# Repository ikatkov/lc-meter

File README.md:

# lc-meter
AADE design LC meter

arduino internal xtal is callibrated to 2ppm with Rigol DS1054Z hardware freq counter, used to be 500ppm off

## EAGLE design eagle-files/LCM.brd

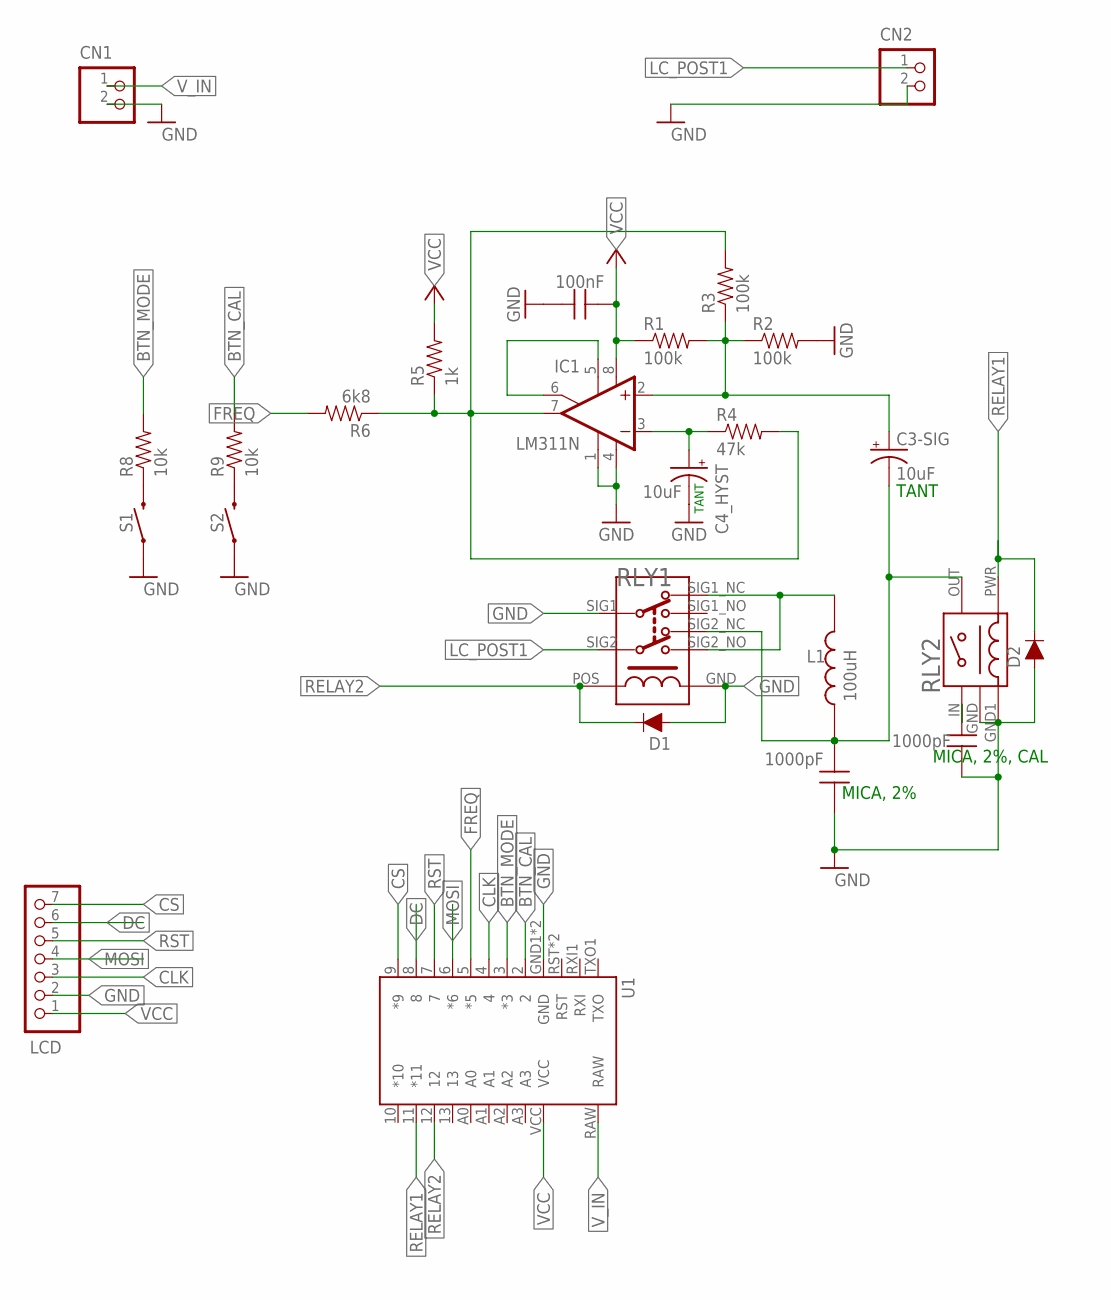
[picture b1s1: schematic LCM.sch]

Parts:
C1, C2: 1000pF; CAPACITOR_PITCH3
C3-SIG, C4_HYST: 10uF; CAPACITOR_POLAR
C5: 100nF; CAPACITOR_PITCH4
CN1, CN2: CONNECTOR-JST-2
D1, D2: DIODEPITCH_3; DIODE_PITCH3
IC1: LM311N; DIL08
L1: 100uH; INDUCTOR-12.5MM
LCD: CONNECTOR-JST-7
R1: 100k; RESISTOR_PITCH5
R2: 100k; RESISTOR_PITCH3
R3: 100k; RESISTOR_PITCH4
R4: 47k; RESISTOR_PITCH3
R5: 1k; RESISTOR_PITCH3
R6: 6k8; RESISTOR_PITCH4
R8, R9: 10k; RESISTOR_PITCH3
RLY1: RELAY_5W-KRELAY-5W-K; RELAY_5W-K
RLY2: REED_RELAY
S1, S2: MOMENTARY-SWITCH-SPST; TACTILE_SWITCH
U1: ARDUINO_PRO_MINI_NO_PRG_HEADER_NOA5NO_A5; ARDUINO_PRO_MINI_IN_HEADER_NOA5

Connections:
BTN_CAL: R9.2, U1.2
BTN_MODE: R8.2, U1.3 (*3)
CLK: LCD.3, U1.4
CS: LCD.7, U1.9 (*9)
DC: LCD.6, U1.8
FREQ: IC1.7 (OUT), R3.2, R4.2, R5.1, R6.1, R6.2, U1.5 (*5)
GND: C1.1 (+), C2.1 (+), C4_HYST.2 (-), C5.1 (+), CN1.2, CN2.2, D1.ANODE (A), D2.ANODE (A), IC1.1 (GND), IC1.4 (V-), LCD.2, R2.2, RLY1.GND (2), RLY1.SIG1, RLY2.GND, RLY2.GND1 (PWR1), S1.1, S1.2 (1), S2.1, S2.2 (1), U1.GND1 (GND), U1.GND4 (GND)
LC_POST1: CN2.1, RLY1.SIG2
MOSI: LCD.4, U1.6 (*6)
unnamed: R8.1, S1.3 (2), S1.4 (2)
unnamed: R9.1, S2.3 (2), S2.4 (2)
PIN2: C3-SIG.1 (+), IC1.2 (+IN), R1.2, R2.1, R3.1
PIN3: C4_HYST.1 (+), IC1.3 (-IN), R4.1
RELAY1: D2.CATHODE (C), RLY2.PWR (PWR2), U1.11 (*11)
RELAY2: D1.CATHODE (C), RLY1.POS (1), U1.12
RST: LCD.5, U1.7
SIG: C2.2 (-), RLY2.IN (SIG1)
SIG2_NC: C1.2 (-), C3-SIG.2 (-), L1.2, RLY1.SIG2_NC (SIG1_NC), RLY2.OUT (SIG2)
SIG2_NO: L1.1, RLY1.SIG1_NC (SIG2_NC), RLY1.SIG2_NO (SIG1_NO)
STROBE: IC1.5 (ON), IC1.6 (ON/STR)
VCC: C5.2 (-), IC1.8 (V+), LCD.1, R1.1, R5.2, U1.VCC
V_IN: CN1.1, U1.RAW

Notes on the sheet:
MICA, 2%
TANT
MICA, 2%, CAL

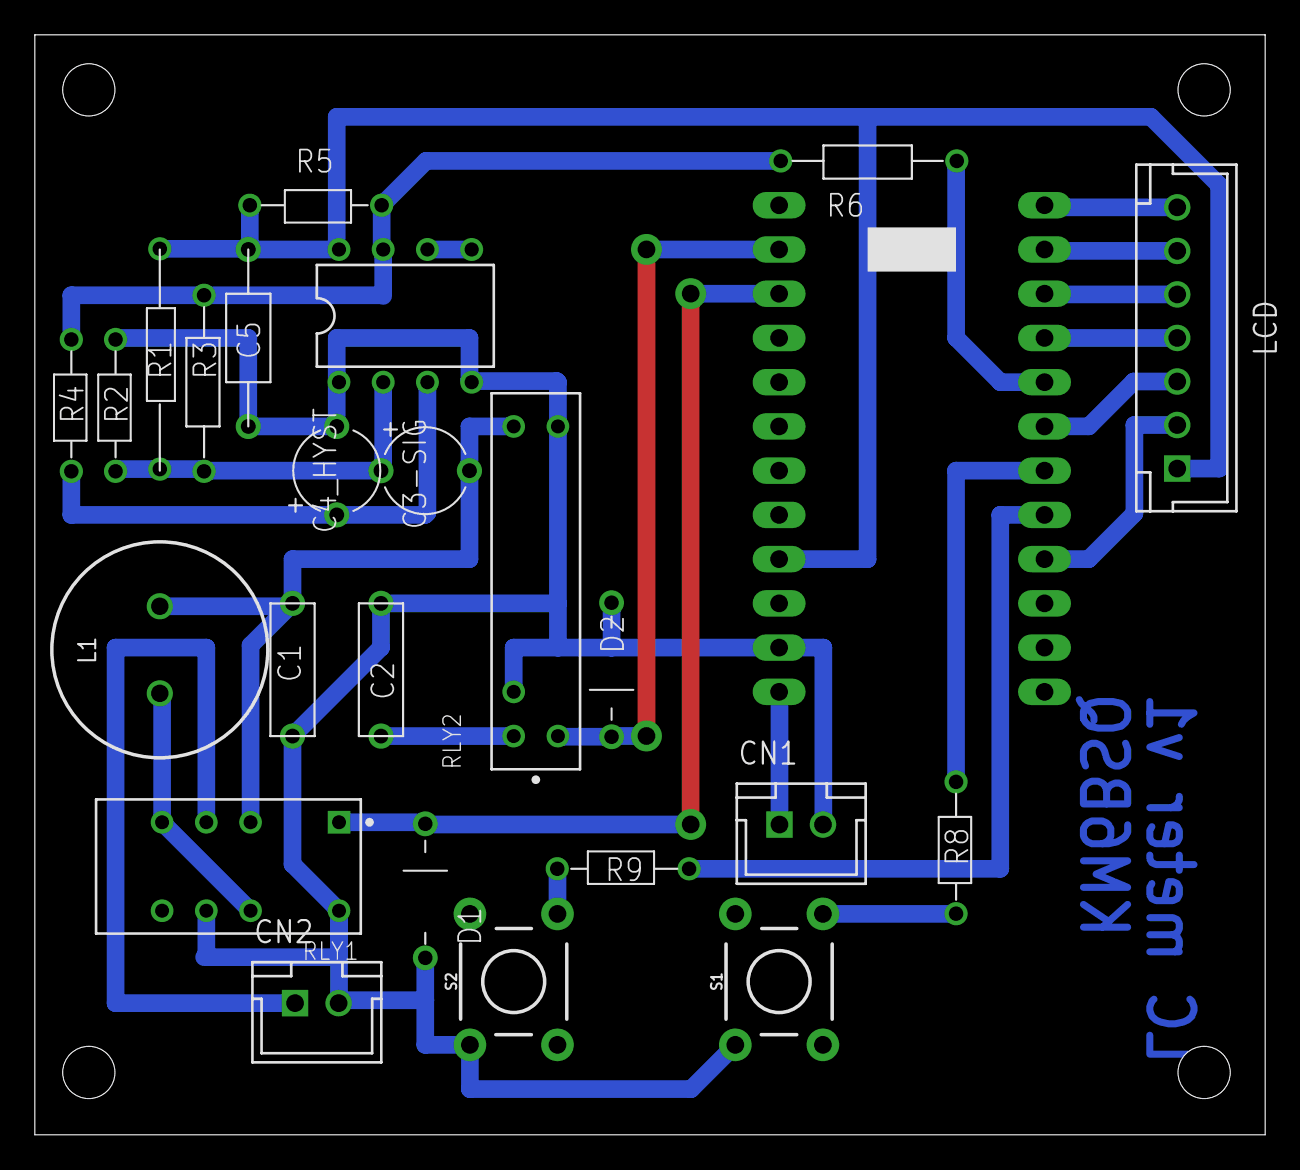
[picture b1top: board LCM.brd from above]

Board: 2 copper layers, 70.6 x 63.2 mm, 25 parts (0 on the bottom side), 22 nets.

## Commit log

2021-11-08 first working version
2021-11-08 wrong file
2021-11-09 not working display
2021-11-09 workin version
2021-11-09 small cleanup
2021-11-09 enclosure for 3d printing
2021-11-09 schematic
2021-11-09 more pictures
2021-11-10 L calibration fix
2021-11-12 remov unused lib dep
